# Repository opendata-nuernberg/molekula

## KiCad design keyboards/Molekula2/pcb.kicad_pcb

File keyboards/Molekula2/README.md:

## Molekula2 keyboard

Reference design using molekula framework PCBs.

Features:

- minY (19x16mm) spacing
- unibody that can be disassembled into two parts for traveling
- 36 keys
- wireless
- nice!view support
- rotary encoder

## Firmware

- [molekula shield](https://github.com/zzeneg/zmk-molekula) with default keymap and ZMK Studio support
- [my custom keymap](https://github.com/zzeneg/zmk-config), can be used as reference if needed

## Bill of materials

### Electrical

- MCU - RP2040 Helios 16M (https://de.aliexpress.com/item/1005010018679591.html)
- 38 Choc switches (https://keeb.supply/collections/choc-switches)
- OR 38 MX switches (https://www.keychron.com/products/gateron-baby-kangaroo-tactile-switch)
- 38 Choc hotswap sockets (https://www.aliexpress.us/item/3256808357010978.html)
- OR 38 MX hotswap sockets (https://www.aliexpress.us/item/3256807045726008.html)
- 38 [SMD SOD-123 1N4148](https://www.aliexpress.us/item/3256809479695335.html) diodes
- 1 [Magnetic connector 12pin](https://www.aliexpress.us/item/3256804525488442.html)
- 1 rotary encoder, [low profile EC12](https://www.aliexpress.com/item/1005003636548797.html) is recommended (no click though). Versions with click often has issues with power consumption, be careful
- 1 [30mm knob](https://www.aliexpress.us/item/3256810097582487.html)
- 2 Vertical 12pin 0.5mm [FFC/FPC connector](https://www.aliexpress.com/item/10000000737049.html)
- 4 Horizontal 12pin 0.5mm [FFC/FPC connector](https://www.aliexpress.com/item/10000348360254.html)
- 2 12pin 0.5mm 5cm [FFC cable](https://www.aliexpress.com/item/1005007561337665.html) - reverse direction
- 2 12pin 0.5mm 5cm [FFC cable](https://www.aliexpress.com/item/1005007561337665.html) - same side (forward direction)
- 1 SMD 4x4x1.5mm [push button](https://www.aliexpress.com/item/32802382507.html)
- 2.54mm female pin [headers](https://www.aliexpress.com/item/4001122376295.html)
- 5pin [headers](https://www.aliexpress.com/item/1005005742644313.html) - source of pins for socketing, and also a connector for nice!view

### Mechanical

- 4/5mm, 6/8mm and 10mm [M2 screws with flat head](https://www.aliexpress.com/item/4001248931159.html) (choose black or silver based on case color/preference)
- [M2 nuts](https://www.aliexpress.com/item/1005001412230125.html)
- M2 3/4mm [heatset inserts](https://www.aliexpress.com/item/1005004624377733.html) - diameter 3.2mm for resin case or 3.5mm for thermoplastic
- [7x1.5mm legs](https://www.aliexpress.com/item/1005002995402961.html)
- [10x3mm magnets](https://www.aliexpress.com/item/1005006802780901.html) - for connecting sides
- [8x2mm magnets](https://www.aliexpress.com/item/1005005426580014.html) - for transportation (optional)

### Optional

- Battery up to 602040 size - this is what I'm using, should be enough but you may try to go bigger (check that there's enough space inside using 3D project)
- _[Optional]_ Vertical 2pin 2.54mm JST [connector](https://www.aliexpress.com/item/1005004938361514.html) for battery

## PCBA

PCBA is recommended, all PCBs are combined into one, BOM and Position files are tested. If you can manually solder FFC connectors with 0.5mm pitch (it's totally doable), ignore PCBA and order PCBs separately.

## Case

See STLs in [./case]() folder. There are separate top/bottom parts for ChocV1/ChocV2/KS-33/MX switches. Also there is left side with and without logo. Separate logo can be printed in another color and inserted.

## Build guide

### Tools

- Soldering iron. Any iron will work, but I highly recommend something small like TS100 or Pinecil with TS-K tip, it's good for SMD soldering
- Solder wire, preferably with lead if you can get one. For EU I recommend this [shop](https://botland.store) and Cynel brand, 0.56mm and 0.9mm
- [Flux](https://www.aliexpress.com/item/1005004675178847.html)
- Flush cutters - be extra careful when cutting pins, always use eye protection
- Hot glue (for nice!view only), instant glue (for resin case only)
- Tweezers (I prefer [reverse](https://www.aliexpress.com/item/1005004188266714.html) instead of regular), pliers, soldering mat, isopropyl alcohol (IPA) and [cotton pads](https://www.aliexpress.com/item/1005003798227116.html) for cleaning

### Preparations

- download [latest firmware](https://github.com/zzeneg/zmk-molekula/actions), flash it to MCU and pair with your PC. It's easier to do it now and also check that MCU actually works
- read through the whole build guide
- break combined PCB into separate parts with pliers, do not sand break-offs

### Soldering

I used PCBA for final version, so I'll skip over FFC/diode soldering. Check my [duet guide](https://github.com/zzeneg/duet/blob/main/guide/readme.md) if needed.

#### Central

Start with MCU socketing (top side is the one with FFC connectors). Prepare MCU headers - you'll need two strips of 12 pins. Don't try to break the header between the pins, instead count the required number of pins, and break in middle of a next pin. Discard that pin and cut the plastic with flush cutters - it'll look much better. Assemble headers like this (using extra headers for stabilization):

Flip carefully and solder all pins starting from corners. I prefer to cut first and then solder but you can cut afterwards as well, just remember to do it as bottom case has only 1.2mm space there. Pins in the middle are used only for encoder click, ignore them if you don't use it.

Pull out 24 pins from RGB headers (I use two pliers for that) and put a piece of masking tape over all headers leaving some space in between for MCU components.

Align MCU holes with headers ignoring top row of holes on the MCU, they are not used/soldered. Insert pins one by one (cut them if you prefer but it's not required). Solder everything starting from corners.

Carefully pull out socketed MCU and remove tape. Now solder the nice!view header and reset button on the back. Finish central with rotary encoder. Done.

#### Magnetic connectors

Prepare two connector PCB with soldered FFC connectors (if soldering manually, make sure black part is facing the side where the breakoffs are). Put them onto magnetic connectors, the one with a "leg" should be on the left side, and FFC's black part should be facing you.

Take them apart and solder without flipping anything. It's a bit tricky because of magnets but doable with two hands. The easiest approach is to add a lot of flux and drag solder across all contacts.

#### Side PCBs

Just solder the hotswap sockets. They are not symmetrical, look at silkscreen on how to place them. Make sure that socket is fully inserted into the PCB. You have use a lot of solder as there are a lot of holes but try to avoid big solder blobs - they may collide with bottom case.

If you want a JST socket for the battery - solder it to the left PCB (JST should be on the top side). Double check the polarity on the battery connector, and do not connect it yet.

#### nice!view

Take a 5-pin header and carefully move pins, leaving around 1.5mm on one side and solder short side to nice!view.

Attach nice!view to the case with hot glue - add more around the pins.

#### Assembly

First insert socketed MCU and attach all FFC cables outside the case and perform basic checks for shorts between BAT/GND/VCC/B+/B-. If everything is ok, solder your battery to the PCB or connect it with JST.

Put screw inserts into the case. For thermoplastics (MJF, PLA, etc) use 3.5mm-wide and look at [this guide](https://docs.bastardkb.com/bg_charybdis/04screw_inserts.html) for detailed instructions on heat inserts. For resin case take 3.2mm inserts and use instant glue (cyanoacrylate) and/or a drill if the holes are too narrow.

Insert 10mm magnets, they should go all the way in so there is no gap between sides, use more force if needed. If loose, add a bit of instant glue inside.

Assemble left side first - insert magnetic connector into the case (bigger one with a "leg") with already attached FFC cable, fix connector PCB in place with 10mm screws. Hot glue your battery to the case, and connect FFC to side PCB. Insert several switches to hold the PCB in place.

Now right side - start with magnetic connector, for this side use 6-8mm screws. Connect FFC cables, carefully put central PCB in place, looking at n!v pins. After that, bend and press the FFC cable going to magnetic connector - it should be flat to hide under encoder knob (the other cable has a lot of place).

Now attach encoder knob. I recommend to put it around 2-3mm higher than the lowest position.

Last step is to add bottom plate, use 4-5mm screws for this.

Done!

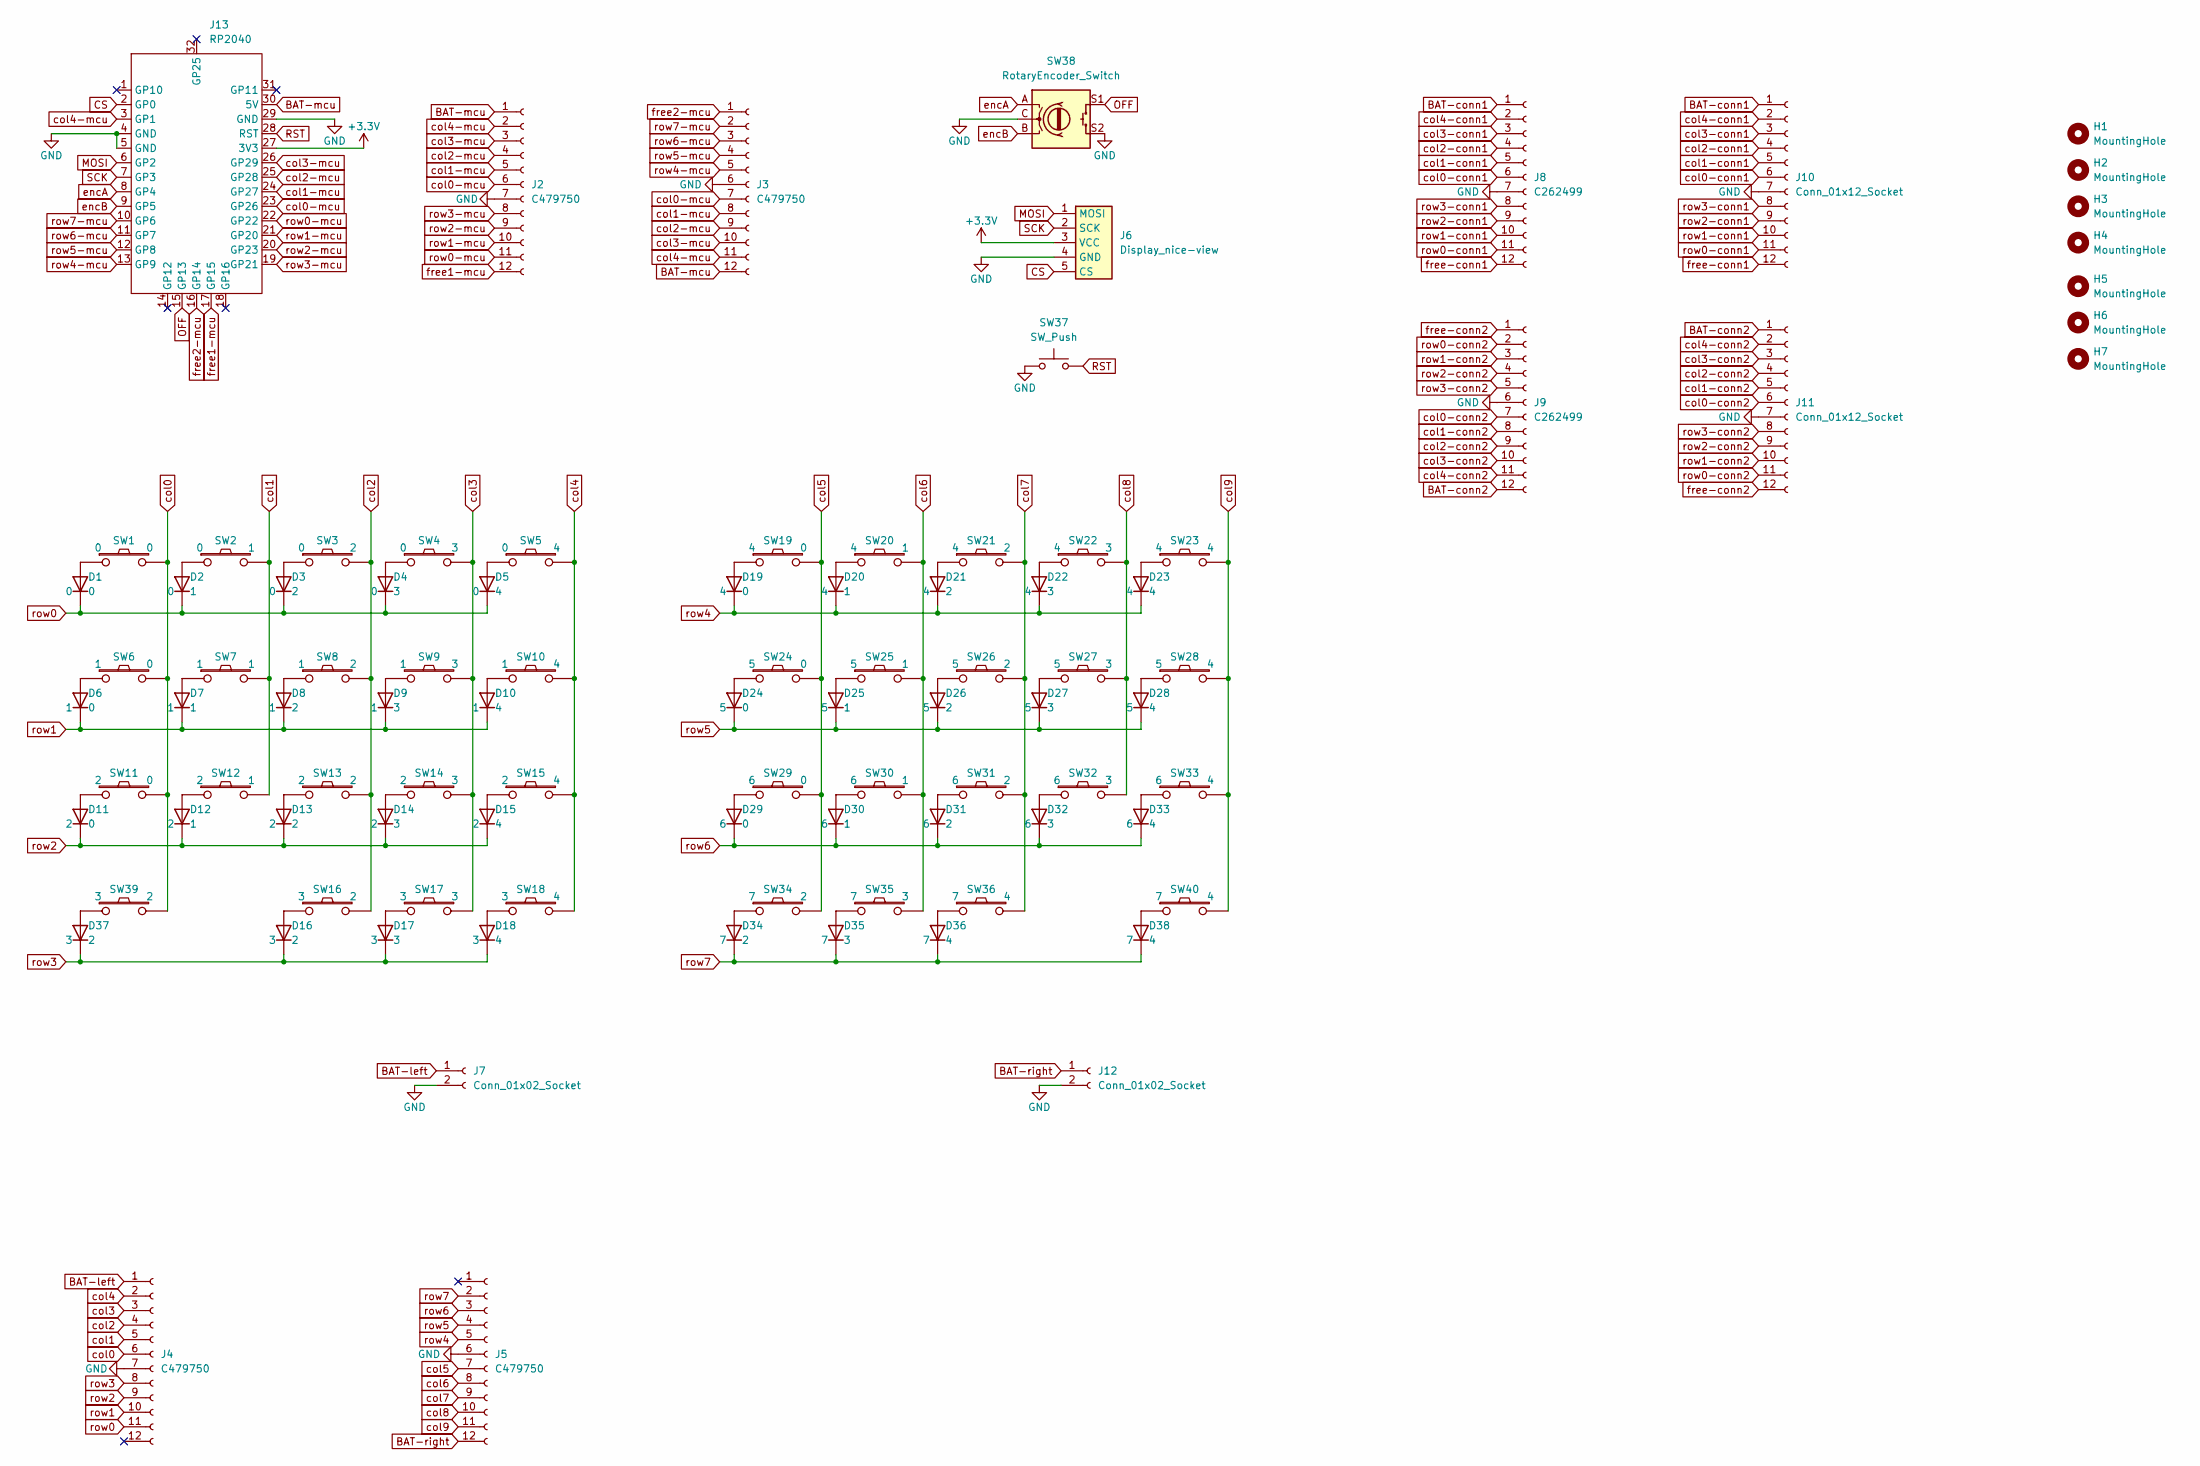
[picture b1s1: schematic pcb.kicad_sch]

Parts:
D1, D2, D3, D4, D5, D6, D7, D8, D9, D10, D11, D12, D13, D14, D15, D16, D17, D18, D19, D20, D21, D22, D23, D24, D25, D26, D27, D28, D29, D30, D31, D32, D33, D34, D35, D36, D37, D38: C81598; Diode_1N4148-SOD123
H1, H2, H3, H4, H5, H6, H7: MountingHole; Hole_M2-solder-nut-2.5
J2, J3, J4, J5: C479750; Connector_FFC-12pin-0.5mm-horizontal
J6: Display_nice-view
J7, J12: Conn_01x02_Socket; Connector_JST-1x02-2.00mm
J8, J9: C262499; Connector_FFC-12pin-0.5mm-vertical
J10, J11: Conn_01x12_Socket; Connector_Magnetic-12pin
J13: RP2040; MCU_rp2040-helios
SW1, SW2, SW3, SW4, SW5, SW6, SW7, SW8, SW9, SW10, SW11, SW12, SW13, SW14, SW15, SW19, SW20, SW21, SW22, SW23, SW24, SW25, SW26, SW27, SW28, SW29, SW30, SW31, SW32, SW33, SW39, SW40: Switch; Switch_MXKSChoc-miny-hotswap-chocv2-3d
SW16, SW17, SW18, SW34, SW35, SW36: Switch; Switch_KSChoc-miny-hotswap-chocv2-3d
SW37: SW_Push; Button_SW_SPST_SKQG_WithoutStem
SW38: RotaryEncoder_Switch; RotaryEncoder_EC11

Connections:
+3.3V: J6.3 (VCC), J13.27 (3V3)
BAT-conn1: J8.1, J10.1
BAT-conn2: J9.12, J11.1
BAT-left: J4.1, J7.1
BAT-mcu: J2.1, J3.12, J13.30 (5V)
BAT-right: J5.12, J12.1
CS: J6.5 (CS), J13.2 (GP0)
GND: J2.7, J3.6, J4.7, J5.6, J6.4 (GND), J7.2, J8.7, J9.6, J10.7, J11.7, J12.2, J13.4 (GND), J13.5 (GND), J13.29 (GND), SW37.1, SW38.C, SW38.S2
MOSI: J6.1 (MOSI), J13.6 (GP2)
unnamed: D1.2 (A), SW1.1
unnamed: D2.2 (A), SW2.1
unnamed: D3.2 (A), SW3.1
unnamed: D4.2 (A), SW4.1
unnamed: D5.2 (A), SW5.1
unnamed: D6.2 (A), SW6.1
unnamed: D7.2 (A), SW7.1
unnamed: D8.2 (A), SW8.1
unnamed: D9.2 (A), SW9.1
unnamed: D10.2 (A), SW10.1
unnamed: D11.2 (A), SW11.1
unnamed: D12.2 (A), SW12.1
unnamed: D13.2 (A), SW13.1
unnamed: D14.2 (A), SW14.1
unnamed: D15.2 (A), SW15.1
unnamed: D16.2 (A), SW16.1
unnamed: D17.2 (A), SW17.1
unnamed: D18.2 (A), SW18.1
unnamed: D19.2 (A), SW19.1
unnamed: D20.2 (A), SW20.1
unnamed: D21.2 (A), SW21.1
unnamed: D22.2 (A), SW22.1
unnamed: D23.2 (A), SW23.1
unnamed: D24.2 (A), SW24.1
unnamed: D25.2 (A), SW25.1
unnamed: D26.2 (A), SW26.1
unnamed: D27.2 (A), SW27.1
unnamed: D28.2 (A), SW28.1
unnamed: D29.2 (A), SW29.1
unnamed: D30.2 (A), SW30.1
unnamed: D31.2 (A), SW31.1
unnamed: D32.2 (A), SW32.1
unnamed: D33.2 (A), SW33.1
unnamed: D34.2 (A), SW34.1
unnamed: D35.2 (A), SW35.1
unnamed: D36.2 (A), SW36.1
unnamed: D37.2 (A), SW39.1
unnamed: D38.2 (A), SW40.1
OFF: J13.15 (GP13), SW38.S1
RST: J13.28 (RST), SW37.2
SCK: J6.2 (SCK), J13.7 (GP3)
col0: J4.6, SW1.2, SW6.2, SW11.2, SW39.2
col0-conn1: J8.6, J10.6
col0-conn2: J9.7, J11.6
col0-mcu: J2.6, J3.7, J13.23 (GP26)
col1: J4.5, SW2.2, SW7.2, SW12.2
col1-conn1: J8.5, J10.5
col1-conn2: J9.8, J11.5
col1-mcu: J2.5, J3.8, J13.24 (GP27)
col2: J4.4, SW3.2, SW8.2, SW13.2, SW16.2
col2-conn1: J8.4, J10.4
col2-conn2: J9.9, J11.4
col2-mcu: J2.4, J3.9, J13.25 (GP28)
col3: J4.3, SW4.2, SW9.2, SW14.2, SW17.2
col3-conn1: J8.3, J10.3
col3-conn2: J9.10, J11.3
col3-mcu: J2.3, J3.10, J13.26 (GP29)
col4: J4.2, SW5.2, SW10.2, SW15.2, SW18.2
col4-conn1: J8.2, J10.2
col4-conn2: J9.11, J11.2
col4-mcu: J2.2, J3.11, J13.3 (GP1)
col5: J5.7, SW19.2, SW24.2, SW29.2, SW34.2
col6: J5.8, SW20.2, SW25.2, SW30.2, SW35.2
col7: J5.9, SW21.2, SW26.2, SW31.2, SW36.2
col8: J5.10, SW22.2, SW27.2, SW32.2
col9: J5.11, SW23.2, SW28.2, SW33.2, SW40.2
encA: J13.8 (GP4), SW38.A
encB: J13.9 (GP5), SW38.B
free1-mcu: J2.12, J13.17 (GP15)
free2-mcu: J3.1, J13.16 (GP14)
free-conn1: J8.12, J10.12
free-conn2: J9.1, J11.12
row0: D1.1 (K), D2.1 (K), D3.1 (K), D4.1 (K), D5.1 (K), J4.11
row0-conn1: J8.11, J10.11
row0-conn2: J9.2, J11.11
row0-mcu: J2.11, J13.22 (GP22)
row1: D6.1 (K), D7.1 (K), D8.1 (K), D9.1 (K), D10.1 (K), J4.10
row1-conn1: J8.10, J10.10
row1-conn2: J9.3, J11.10
row1-mcu: J2.10, J13.21 (GP20)
row2: D11.1 (K), D12.1 (K), D13.1 (K), D14.1 (K), D15.1 (K), J4.9
row2-conn1: J8.9, J10.9
row2-conn2: J9.4, J11.9
row2-mcu: J2.9, J13.20 (GP23)
row3: D16.1 (K), D17.1 (K), D18.1 (K), D37.1 (K), J4.8
row3-conn1: J8.8, J10.8
row3-conn2: J9.5, J11.8
row3-mcu: J2.8, J13.19 (GP21)
row4: D19.1 (K), D20.1 (K), D21.1 (K), D22.1 (K), D23.1 (K), J5.5
row4-mcu: J3.5, J13.13 (GP9)
row5: D24.1 (K), D25.1 (K), D26.1 (K), D27.1 (K), D28.1 (K), J5.4
row5-mcu: J3.4, J13.12 (GP8)
row6: D29.1 (K), D30.1 (K), D31.1 (K), D32.1 (K), D33.1 (K), J5.3
row6-mcu: J3.3, J13.11 (GP7)
row7: D34.1 (K), D35.1 (K), D36.1 (K), D38.1 (K), J5.2
row7-mcu: J3.2, J13.10 (GP6)

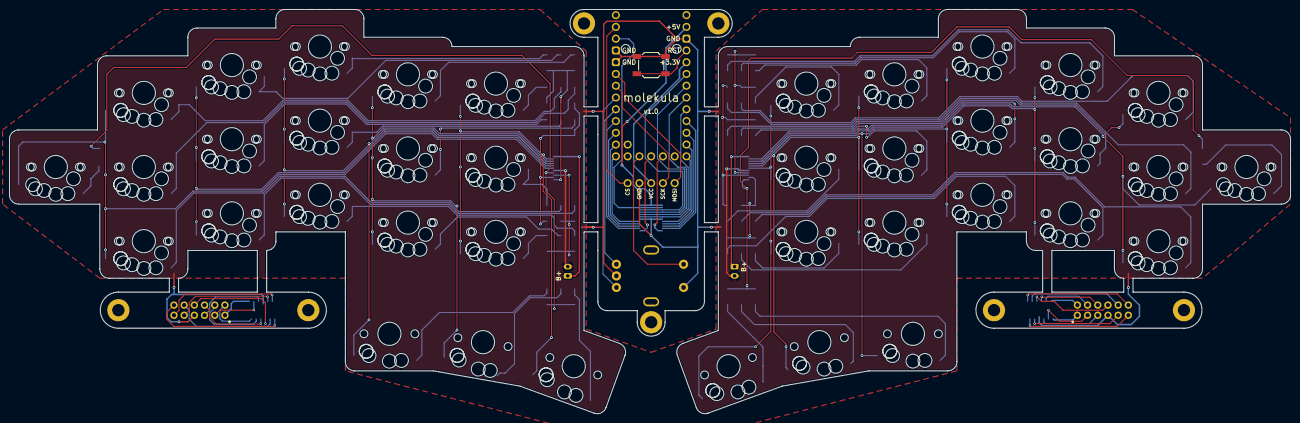
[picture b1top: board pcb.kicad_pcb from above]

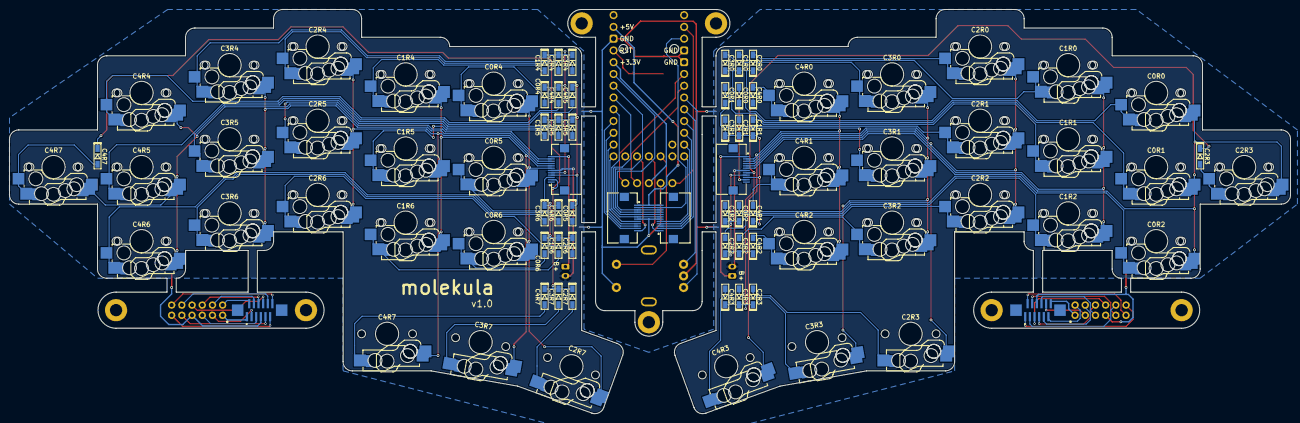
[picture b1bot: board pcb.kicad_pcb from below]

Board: 2 copper layers, 276.5 x 87.2 mm, 97 parts (54 on the bottom side), 105 nets.

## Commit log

2025-12-29 feat: add 2 more keys to the upper row and updated bom
2025-12-29 (add) rp2040
2025-12-29 feat: change MCU to RP2040
2025-12-30 (add) updated production files
2025-12-30 (add) bom.zip
2025-12-31 (add) part order list.
2026-01-31 add print files and keycap models
